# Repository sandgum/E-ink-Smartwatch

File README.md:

# Triangulate ES_01 E-ink Watch
---
An ultra-thin ESP32S3-based smartwatch (at just 5mm thick at its thickest point) which uses an E-ink display and two OLEDs to display information while consuming a small amount of power. The main E-ink panel is touch-enabled, with the two additional OLED panels above and below it displaying auxiliary information, such as notifications, background activities etc. 
The watch has built-in heart rate and spO2 sensing via an Analog Devices MAX30102, high-precision smart movement sensing via a Bosch BH260AP IMU and a Bosch BMP585 barometric pressure sensor.

*ACKNOWLEDGMENT: Most of the materials and the human hand model you see in the renders are not my own work, but is Royalty-free or CC0 licensed work legitimately downloaded from BlenderKit using their free plan*

---

To top it all off, the ES_01 is completely workout-friendly, with rubberised sides and no pesky side buttons that get pressed mid-pushup (Every physical input is at the top of the watch)!
The watch features a sleek design, with each component being laid out single file and in its own separate segment of the watch. These segments can all bend around the watch, preserving a uniform thickness all around, which also adds the benefit of being aesthetically pleasing.
The main microcontroller running the watch is an Espressif ESP32-S3 running with Bluetooth LE capabilities, which also allow for it to sync with a smartphone to relay notifications, workout, and weather data etc. through firmware based on ESP-IDF and host smartphone software for iPhone based on Swift (Coming soon, and Android support will come later!)

---
## PCB:

-  4 layers
-  Flex PCB
-  Single-sided component placement
-  0.2mm board thickness
-  Added 0.1mm FR4 stiffeners
-  All resistors and capacitors are 0402 size

*Schematics:*

*PCB Layout and render:*

---

## Enclosure:

- Main cases and top plates of easch segment 3D printed using an SLA/MSLA printer
- Main cases printed in Black resin from JLC3DP (can substitute with any rigid resin)
- Top plates printed in LEDO 6060 resin from JLC3DP (can substitute with any rigid resin)
- Bottom plates for OLED segments are CNC machined from 6061 Aluminium by JLCCNC (can substitute with any rigid material or also with SLA/MSLA printed resin)
- Bottom plate for main E-ink segment 3D printed using an SLM printer in 316L stainless steel (can substitute with other rigid metal with high thermal conductivity)

---

## Assembly instructions:

1. Use the solder stencil to squeegee solder paste onto main PCB
2. Place each component onto its respective pads on the main PCB
3. Use a hotplate or a reflow oven to reflow the solder paste underneath the components
4. Hand-solder a thin insulated wire (enamel insulated or rubber insulated) connecting the pads "BATT1_WIRE" together on the PCB
5. Create a solder bridge connecting the pads "GND_TO_GNDIO" and "GNDIO_TO_GND"
6. Create a solder bridge connecting the pads "GND_TO_GNDPWR" and "GNDPWR_TO_GND"
7. Assemble the two "end battery" segments by threading battery wires through them, placing the battery in and attaching the top plates to their respective main cases with superglue
8. Assemble the other battery segment and the haptic module segment in the same way, but thread the "end battery" wires through the dedicated channels in these segments, you should have two sets of two segments with four wires coming out of each set of segments
9. Take the main cases of the OLED modules and superglue the OLED displays into the top of each, making sure the flex cables poke through their dedicated holes
10. Do the same with the E-ink segment and the E-ink display
11. Attach each remaining top plate to its respective main case using superglue
12. Place and superglue the main Flex PCB into the bottom of the E-ink segment and the two OLED segments. The back of the PCB should face the displays
13. Thread the wires from the two sets of segments from step 8 through the holes in the side of the OLED modules and hand-solder the wires onto their respective pads
14. Plug in the flex cables from each display into thir respective FPC connectors on the main PCB
15. Superglue the bottom panels for the OLED segments onto their respective main cases
16. Apply thermal paste on the ESP32-S3 chip on the main PCB
17. Superglue threaded inserts in the two dedicated holes in the corners of the bottom panel for the E-ink segment
19. Superglue the bottom panel to the main case of the E-ink segment
20. Screw two screws into the holes in the top case of the E-ink segment until they mesh with the threaded inserts from the previous step
21. Take two more screws and cut off their entire threaded sections until just the heads remain. Superglue those heads in the holes in the other two corners of the top panel of the E-ink segment
22. Superglue the side TPU pieces to the sides of all the segments
23. Plug in a patch antenna into the exposed U.FL port on the back of the watch, guide the cable through its designated groove, and stick the patch antenna somewhere on the watch

---
## Bill of materials:

*Electronic Components: (Order quantities account for minimum order quantity of parts from the chosen retailer)*

| Manufacturer Part Number | Mfr.                        | Order Qty. | Unit Price(USD) | Ext.Price(USD) | Package                               | Description                                                                                                                | Product Link                                       |
|--------------------------|-----------------------------|------------|-----------------|----------------|---------------------------------------|----------------------------------------------------------------------------------------------------------------------------|----------------------------------------------------|
| CC0402JRNPO9BN110        | YAGEO                       | 100        | 0.0012          | 0.12           | 0402                                   | 11pF ±5% 50V Ceramic Capacitor NP0 0402                                                                                    | https://www.lcsc.com/product-detail/C527000.html   |
| GRM155R61E475ME15D       | muRata                      | 20         | 0.0377          | 0.75           | 0402                                   | 4.7uF ±20% 25V Ceramic Capacitor X5R 0402                                                                                  | https://www.lcsc.com/product-detail/C2858031.html  |
| ESP32-S3                 | ESPRESSIF                   | 1          | 2.7791          | 2.78           | QFN-56-EP(7x7)                         | 150Mbps 2.4GHz 2.412GHz~2.484GHz QFN-56-EP(7x7) RF Transceiver ICs RoHS                                                    | https://www.lcsc.com/product-detail/C2913192.html  |
| 2328702-6                | TE Connectivity             | 5          | 0.1654          | 0.83           | SMD,P=0.5mm,Surface Mount,Right Angle  | FFC/FPC Connector 6 Position 0.5mm Pitch Double-Sided Contacts, Top and Bottom Entry Surface Mount, Right Angle -40℃~+85℃  | https://www.lcsc.com/product-detail/C3151647.html  |
| FFC2B28-24-G             | Global Connector Technology | 1          | 0.5754          | 0.58           | SMD,P=0.5mm,Surface Mount,Right Angle  | FFC/FPC Connector 24 Position 0.5mm Pitch Double-Sided Contacts, Top and Bottom Entry Surface Mount, Right Angle -25℃~+85℃ | https://www.lcsc.com/product-detail/C3151659.html  |
| BHI260AP                 | Bosch                       | 1          | 8.7882          | 8.79           | LGA-44                                 | LGA-44 IMUs (Inertial Measurement Units) RoHS                                                                              | https://www.lcsc.com/product-detail/C3288651.html  |
| SI1308EDL-T1-GE3         | VISHAY                      | 5          | 0.1324          | 0.66           | SOT-323                                | N-Channel 30V 1.5A 0.4W Surface Mount SOT-323                                                                              | https://www.lcsc.com/product-detail/C469327.html   |
| XC6206P302MR             | HXY MOSFET                  | 50         | 0.0154          | 0.77           | SOT-23                                 | Linear Voltage Regulator IC Positive Fixed 1 Output 300mA SOT-23                                                           | https://www.lcsc.com/product-detail/C5148691.html  |
| MBR0530                  | Huixin                      | 20         | 0.0205          | 0.41           | SOD-123                                | 5.5A 30V 500mV@500mA 500mA SOD-123 Single Diodes RoHS                                                                     | https://www.lcsc.com/product-detail/C49435625.html |
| 0402WGF1004TCE           | UNI-ROYAL                   | 100        | 0.0006          | 0.06           | 0402                                   | 1MΩ ±1% 62.5mW 0402 Thick Film Resistor                                                                                    | https://www.lcsc.com/product-detail/C26083.html    |
| CL05A105KA5NQNC          | Samsung Electro-Mechanics   | 100        | 0.0030          | 0.30           | 0402                                   | 1uF ±10% 25V Ceramic Capacitor X5R 0402                                                                                    | https://www.lcsc.com/product-detail/C52923.html    |
| XL2EL89CPI-111YLC-40M    | YXC Crystal Oscillators     | 10         | 0.0578          | 0.58           | SMD3225-4P                             | Crystal 40MHz ±10ppm 15pF SMD3225-4P                                                                                       | https://www.lcsc.com/product-detail/C5444549.html  |
| TS-1088-AR02016          | XUNPU                       | 10         | 0.0421          | 0.42           | SMD,4x3mm                              | Tactile Switch SPST 160gf 2mm SMD (SMT) Tab 4mm x 3mm Surface Mount                                                        | https://www.lcsc.com/product-detail/C720477.html   |
| BSS138                   | R+O                         | 50         | 0.0170          | 0.85           | SOT-23                                 | N-Channel 50V 340mA 350mW Surface Mount SOT-23                                                                             | https://www.lcsc.com/product-detail/C7420339.html  |
| TCR2EF33,LM(CT           | TOSHIBA                     | 5          | 0.0829          | 0.41           | TSOT-25                                | Positive Fixed 3.3V TSOT-25 Voltage Regulators - Linear, Low Drop Out (LDO) Regulators RoHS                                | https://www.lcsc.com/product-detail/C843273.html   |
| LQG15HS3N3S02D           | muRata                      | 100        | 0.0076          | 0.76           | 0402                                   | 800mA 3.3nH 125mΩ 0402 Fixed Inductors RoHS                                                                                | https://www.lcsc.com/product-detail/C86064.html    |
| MRA4003T3G               | onsemi                      | 10         | 0.0873          | 0.87           | SMA(DO-214AC)                          | Diode 300V 1A Surface Mount SMA(DO-214AC)                                                                                  | https://www.lcsc.com/product-detail/C94410.html    |
| DRV2605LDGSR             | TI                          | 1          | 1.2502          | 1.3            | VSSOP-10-0.5mm                         | 2V~5.2V I2C VSSOP-10-0.5mm Motor Drivers, Controllers RoHS                                                                 | https://www.lcsc.com/product-detail/C527464.html   |
| LQG15HS2N0S02D           | muRata                      | 100        | 0.0081          | 0.81           | 0402                                   | 900mA 2nH 90mΩ 0402 Fixed Inductors RoHS                                                                                   | https://www.lcsc.com/product-detail/C18216.html    |
| 0402WGF5603TCE           | UNI-ROYAL                   | 100        | 0.0005          | 0.05           | 0402                                   | 560kΩ ±1% 62.5mW 0402 Thick Film Resistor                                                                                  | https://www.lcsc.com/product-detail/C132339.html   |
| CL05B103KB5NNNC          | Samsung Electro-Mechanics   | 100        | 0.0014          | 0.14           | 0402                                   | 10nF ±10% 50V Ceramic Capacitor X7R 0402                                                                                   | https://www.lcsc.com/product-detail/C15195.html    |
| 0402B102K500NT           | FH                          | 100        | 0.0011          | 0.11           | 0402                                   | 1nF ±10% 50V Ceramic Capacitor X7R 0402                                                                                    | https://www.lcsc.com/product-detail/C1523.html     |
| CL05B104KO5NNNC          | Samsung Electro-Mechanics   | 100        | 0.0012          | 0.12           | 0402                                   | 100nF ±10% 16V Ceramic Capacitor X7R 0402                                                                                  | https://www.lcsc.com/product-detail/C1525.html     |
| 0402CG1R0C500NT          | FH                          | 100        | 0.0012          | 0.12           | 0402                                   | 1pF 50V Ceramic Capacitor C0G 0402                                                                                         | https://www.lcsc.com/product-detail/C1550.html     |
| CL05A106MQ5NUNC          | Samsung Electro-Mechanics   | 100        | 0.0044          | 0.44           | 0402                                   | 10uF ±20% 6.3V Ceramic Capacitor X5R 0402                                                                                  | https://www.lcsc.com/product-detail/C15525.html    |
| CL05B224KO5NNNC          | Samsung Electro-Mechanics   | 100        | 0.0044          | 0.44           | 0402                                   | 220nF ±10% 16V Ceramic Capacitor X7R 0402                                                                                  | https://www.lcsc.com/product-detail/C16772.html    |
| BMP585                   | Bosch                       | 1          | 2.2083          | 2.21           | LGA-9(3.3x3.3)                         | 30Kpa~1.25bar LGA-9(3.3x3.3) Pressure Sensors, Transducers RoHS                                                            | https://www.lcsc.com/product-detail/C18184976.html |
| 0402WGF1001TCE           | UNI-ROYAL                   | 100        | 0.0006          | 0.06           | 0402                                   | 1kΩ ±1% 62.5mW 0402 Thick Film Resistor                                                                                    | https://www.lcsc.com/product-detail/C11702.html    |
| LD39200PU33R             | ST                          | 1          | 1.2693          | 1.27           | DFN-6(3x3)                             | Positive Fixed 3.3V DFN-6(3x3) Voltage Regulators - Linear, Low Drop Out (LDO) Regulators RoHS                             | https://www.lcsc.com/product-detail/C222192.html   |
| CL05A475MP5NRNC          | Samsung Electro-Mechanics   | 50         | 0.0048          | 0.24           | 0402                                   | 4.7uF ±20% 10V Ceramic Capacitor X5R 0402                                                                                  | https://www.lcsc.com/product-detail/C23733.html    |
| 0402WGF220JTCE           | UNI-ROYAL                   | 100        | 0.0007          | 0.07           | 0402                                   | 22Ω ±1% 62.5mW 0402 Thick Film Resistor                                                                                    | https://www.lcsc.com/product-detail/C25092.html    |
| 0402WGF220KTCE           | UNI-ROYAL                   | 100        | 0.0009          | 0.09           | 0402                                   | 2.2Ω ±1% 62.5mW 0402 Thick Film Resistor                                                                                   | https://www.lcsc.com/product-detail/C25101.html    |
| 0402WGF1002TCE           | UNI-ROYAL                   | 100        | 0.0006          | 0.06           | 0402                                   | 10kΩ ±1% 62.5mW 0402 Thick Film Resistor                                                                                   | https://www.lcsc.com/product-detail/C25744.html    |
| 0402WGF2201TCE           | UNI-ROYAL                   | 100        | 0.0006          | 0.06           | 0402                                   | 2.2kΩ ±1% 62.5mW 0402 Thick Film Resistor                                                                                  | https://www.lcsc.com/product-detail/C25879.html    |
| 0402WGF4701TCE           | UNI-ROYAL                   | 100        | 0.0006          | 0.06           | 0402                                   | 4.7kΩ ±1% 62.5mW 0402 Thick Film Resistor                                                                                  | https://www.lcsc.com/product-detail/C25900.html    |
| ANR4012T470M             | APV                         | 10         | 0.0517          | 0.52           | SMD,4x4mm                              | 47uH Magnetic Shielded Inductor 500mA SMD,4x4mm Fixed Inductors RoHS                                                       | https://www.lcsc.com/product-detail/C7497063.html  |
| MAX30102EFD+T            | MAXIM                       | 1          | 13.7281         | 13.73          | OESIP-14                               | I2C OESIP-14 Specialized Sensors RoHS                                                                                      | https://www.lcsc.com/product-detail/C6454833.html  |
| LW06121                  | WENDA                       | 100        | 0.07            | 7              | SMD,P=0.62mm,Surface Mount,Right Angle | 1.2H 14Pin 0.62mm Pitch OLED FPC/FFC Upper Contact Pull-Out Horizontal SMD Flat Connector                                 | https://www.alibaba.com/product-detail/WENDA-LW06121-1-2H-14Pin-0_1601292173873.html |
| 1N4148                   | onsemi                      | 50         | 0.0221          | 1.11           | DO-35                                  | Diode 100V 200mA Through Hole DO-35                                                                                        | https://www.lcsc.com/product-detail/C258182.html   |
| GDEY0154D67-T03          | Goodisplay                  | 1          | 11.32           | 11.32          | -                                      | 1.54Inch Touch E-Paper 200x200 E-Ink Display                                                                               | https://www.aliexpress.com/item/1005005200574055.html |
| SSD1306                  | -                           | 2          | 0.72            | 1.44           | -                                      | 0.91 Inch I2C OLED Module                                                                                                  | https://www.aliexpress.com/item/1005004415958608.html?spm=a2g0o.tesla.0.0.4820nU7CnU7Cr1&pdp_npi=6%40dis%21AUD%21AU%241.39%21AU%241.05%21%21%21%21%21%402103122117624689217517794e3108%2112000046550658291%21btfpre%21%21%21%211%210%21&afTraceInfo=1005004415958608__pc__c_ppc_item_bridge_pc_main__vt8pak6__1762468921809 |
| 401225                   | -                           | 3          | 2.66            | 7.98           | -                                      | 3.7V 100mAh Lithium Polymer Lipo Rechargeable Battery                                                                      | https://www.aliexpress.com/item/1005006129236699.html?spm=a2g0o.cart.0.0.157538daxZfUfb&mp=1&pdp_npi=5%40dis%21AUD%21AUD%204.73%21AUD%204.02%21%21AUD%204.02%21%21%21%402103212317648973370843232e461d%2112000035892453159%21ct%21AU%216047249797%21%211%210 |
| 0619AAC                  | -                           | 1          | 3.06            | 3.06           | -                                      | Brushless X-axis 1.2V 100mA Max Precision Vibration Motor                                                                  | https://www.aliexpress.com/item/1005006421331249.html?spm=a2g0o.tesla.0.0.24f1nmtsnmts4h&pdp_npi=6%40dis%21AUD%21AU%244.13%21AU%241.54%21%21%21%21%21%402101d9ef17624709252885249e887e%2112000049883253246%21btfpre%21%21%21%211%210%21&afTraceInfo=1005006421331249__pc__c_ppc_item_bridge_pc_main__epipcn9__1762470925359 |
| TS-A002                  | -                           | 20         | 0.069           | 1.38           | -                                      | Momentary Tact Switch SMD                                                                                                  | https://www.aliexpress.com/item/1005008702742151.html?spm=a2g0o.cart.0.0.785138daOe1hVa&mp=1&pdp_npi=5%40dis%21USD%21USD%201.38%21USD%201.38%21%21USD%201.38%21%21%21%4021033d1217668082665115137ee51b%2112000046642944142%21ct%21AU%216047249797%21%211%210 |
| -                        | -                           | 50         | 0.0264          | 1.32           | -                                      | M1.4 Torx countersunk machine screw 4mm length                                                                             | https://www.aliexpress.com/item/33006942612.html?spm=a2g0o.cart.0.0.172438dayDrOXJ&mp=1&pdp_npi=5%40dis%21USD%21USD%201.32%21USD%201.32%21%21USD%201.32%21%21%21%402103212317668074428231957e8041%2167012387977%21ct%21AU%216047249797%21%211%210 |
| -                        | -                           | 50        | 0.0244          | 1.22            | -                                      | M1.4 Brass threaded inserts 1.5mm length                                                                                   | https://www.aliexpress.com/item/1005007653131713.html?spm=a2g0o.cart.0.0.785138daOe1hVa&mp=1&pdp_npi=5%40dis%21USD%21USD%201.36%21USD%201.22%21%21USD%201.22%21%21%21%402101e2b217668079638444750e2ddc%2112000041667111405%21ct%21AU%216047249797%21%211%210&pdp_ext_f=%7B%22cart2PdpParams%22%3A%7B%22pdpBusinessMode%22%3A%22retail%22%7D%7D |

Total: $85.43 USD

*Manufactured Components*

| Description | Manufacturer | Material | Price (USD) |
|-------------|--------------|----------|-------------|
| 3D Printed Enclosure Main Cases | JLC3DP | Black Resin | 7.05 |
| 3D Printed Enclosure Top Plates | JLC3DP | LEDO 6060 Resin | 2.11 |
| CNC Machined OLED Segment Bottom Plates | JLCCNC | Aluminium 6061 | 17.46 |
| SLM 3D Printed Main Segment Bottom Plate | JLC3DP | 316L Stainless Steel | 8.39 |
| Main 4-layer Flex PCB | JLCPCB | Yellow 0.2mm Polyimide with 0.1mm FR4 Stiffener | 94.00 |
| SMD Stencil for Main Flex PCB | JLCPCB | Steel | 7.47 |

Total: $136.48 USD

---
## Grand Total (Excl. Shipping): $221.91 USD
---

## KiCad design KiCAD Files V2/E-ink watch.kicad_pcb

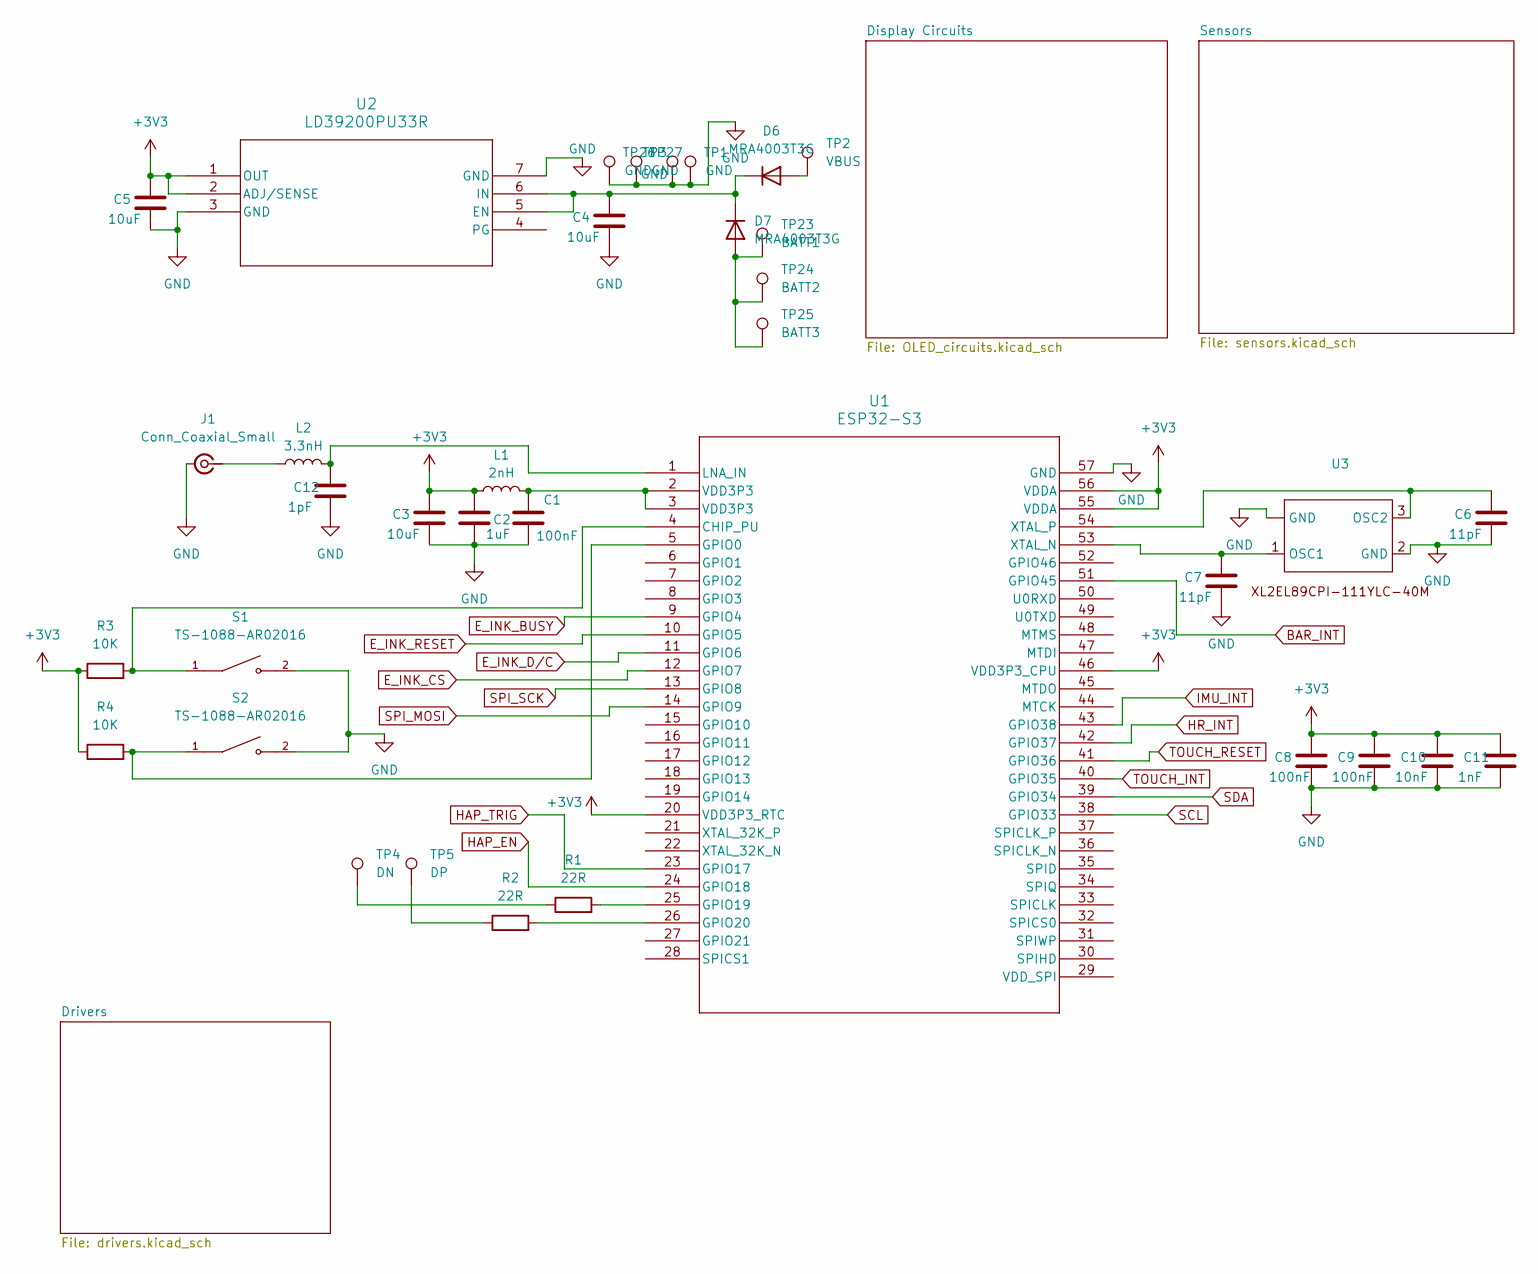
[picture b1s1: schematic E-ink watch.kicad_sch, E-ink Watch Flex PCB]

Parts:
C1, C8, C9: 100nF; C_0402_1005Metric_Pad0.74x0.62mm_HandSolder
C2: 1uF; C_0402_1005Metric_Pad0.74x0.62mm_HandSolder
C3, C4, C5: 10uF; C_0402_1005Metric_Pad0.74x0.62mm_HandSolder
C6, C7: 11pF; C_0402_1005Metric_Pad0.74x0.62mm_HandSolder
C10: 10nF; C_0402_1005Metric_Pad0.74x0.62mm_HandSolder
C11: 1nF; C_0402_1005Metric_Pad0.74x0.62mm_HandSolder
C12: 1pF; C_0402_1005Metric_Pad0.74x0.62mm_HandSolder
D6, D7: MRA4003T3G; D_SMA
J1: Conn_Coaxial_Small; U.FL_Hirose_U.FL-R-SMT-1_Vertical
L1: 2nH; L_0402_1005Metric_Pad0.77x0.64mm_HandSolder
L2: 3.3nH; L_0402_1005Metric_Pad0.77x0.64mm_HandSolder
R1, R2: 22R; R_0402_1005Metric_Pad0.72x0.64mm_HandSolder
R3, R4: 10K; R_0402_1005Metric_Pad0.72x0.64mm_HandSolder
S1, S2: TS-1088-AR02016; SW_TS-1088-AR02016; PARTREV N/A
TP1, TP3, TP26, TP27: GND; TestPoint_Pad_1.5x1.5mm
TP2: VBUS; TestPoint_Pad_1.5x1.5mm
TP4: DN; TestPoint_Pad_1.5x1.5mm
TP5: DP; TestPoint_Pad_1.5x1.5mm
TP23: BATT1; TestPoint_Pad_1.5x1.5mm
TP24: BATT2; TestPoint_Pad_1.5x1.5mm
TP25: BATT3; TestPoint_Pad_1.5x1.5mm
U1: ESP32-S3; QFN56_7X7_EXP
U2: LD39200PU33R; SON_DFN6_3X3_STM
U3: Untitled

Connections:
+3V3: C2.1, C3.1, C5.1, C8.1, C9.1, C10.1, C11.1, L1.1, R3.1, R4.1, U1.20 (VDD3P3_RTC), U1.46 (VDD3P3_CPU), U1.55 (VDDA), U1.56 (VDDA), U2.1 (OUT), U2.2 (ADJ/SENSE); also elsewhere on the board
BAR_INT: U1.51 (GPIO45); also elsewhere on the board
E_INK_BUSY: U1.9 (GPIO4); also elsewhere on the board
E_INK_CS: U1.12 (GPIO7); also elsewhere on the board
E_INK_D/C: U1.11 (GPIO6); also elsewhere on the board
E_INK_RESET: U1.10 (GPIO5); also elsewhere on the board
GND: C1.2, C2.2, C3.2, C4.2, C5.2, C6.2, C7.2, C8.2, C9.2, C10.2, C11.2, C12.2, J1.2 (Ext), S1.2, S2.2, TP1.1, TP3.1, TP26.1, TP27.1, U1.57 (GND), U2.3 (GND), U2.7 (GND), U3. (GND), U3.2 (GND), U3.4; also elsewhere on the board
HAP_EN: U1.24 (GPIO18); also elsewhere on the board
HAP_TRIG: U1.23 (GPIO17); also elsewhere on the board
HR_INT: U1.42 (GPIO37); also elsewhere on the board
IMU_INT: U1.43 (GPIO38); also elsewhere on the board
unnamed: C1.1, L1.2, U1.2 (VDD3P3), U1.3 (VDD3P3)
unnamed: D6.2 (A), TP2.1
unnamed: C4.1, D6.1 (K), D7.1 (K), U2.5 (EN), U2.6 (IN)
unnamed: D7.2 (A), TP23.1, TP24.1, TP25.1
unnamed: J1.1 (In), L2.1
unnamed: R1.1, TP4.1
unnamed: R2.1, TP5.1
unnamed: R3.2, S1.1, U1.4 (CHIP_PU)
unnamed: R4.2, S2.1, U1.5 (GPIO0)
unnamed: R1.2, U1.25 (GPIO19)
unnamed: R2.2, U1.26 (GPIO20)
unnamed: C12.1, L2.2, U1.1 (LNA_IN)
unnamed: C7.1, U1.53 (XTAL_N), U3.1 (OSC1)
unnamed: C6.1, U1.54 (XTAL_P), U3.3 (OSC2)
SCL: U1.38 (GPIO33); also elsewhere on the board
SDA: U1.39 (GPIO34); also elsewhere on the board
SPI_MOSI: U1.14 (GPIO9); also elsewhere on the board
SPI_SCK: U1.13 (GPIO8); also elsewhere on the board
TOUCH_INT: U1.40 (GPIO35); also elsewhere on the board
TOUCH_RESET: U1.41 (GPIO36); also elsewhere on the board

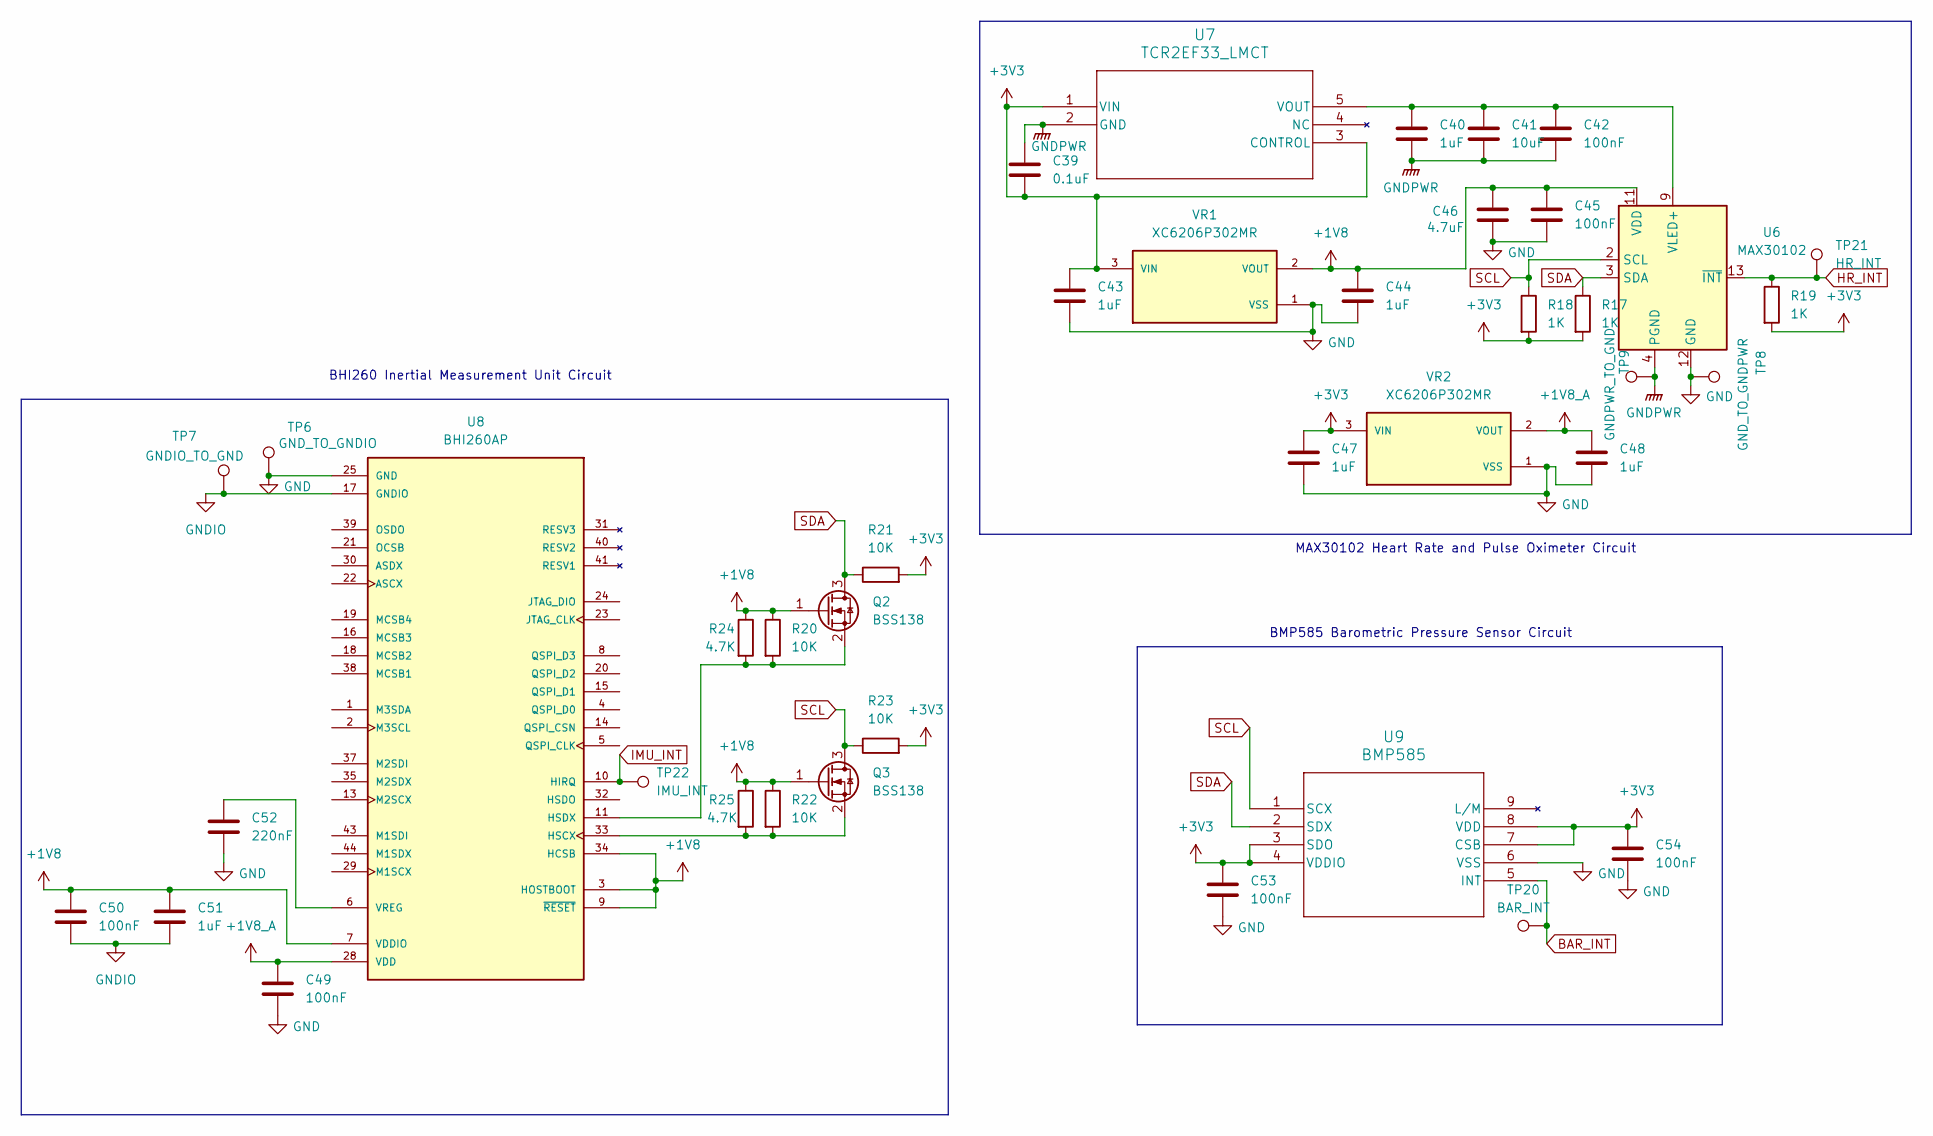
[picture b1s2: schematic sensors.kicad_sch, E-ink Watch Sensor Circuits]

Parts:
C39: 0.1uF; C_0402_1005Metric_Pad0.74x0.62mm_HandSolder
C40, C43, C44, C47, C48, C51: 1uF; C_0402_1005Metric_Pad0.74x0.62mm_HandSolder
C41: 10uF; C_0402_1005Metric_Pad0.74x0.62mm_HandSolder
C42, C45, C49, C50, C53, C54: 100nF; C_0402_1005Metric_Pad0.74x0.62mm_HandSolder
C46: 4.7uF; C_0402_1005Metric_Pad0.74x0.62mm_HandSolder
C52: 220nF; C_0402_1005Metric_Pad0.74x0.62mm_HandSolder
Q2, Q3: BSS138; SOT-23
R17, R18, R19: 1K; R_0402_1005Metric_Pad0.72x0.64mm_HandSolder
R20, R21, R22, R23: 10K; R_0402_1005Metric_Pad0.72x0.64mm_HandSolder
R24, R25: 4.7K; R_0402_1005Metric_Pad0.72x0.64mm_HandSolder
TP6: GND_TO_GNDIO; TestPoint_Pad_1.5x1.5mm
TP7: GNDIO_TO_GND; TestPoint_Pad_1.5x1.5mm
TP8: GND_TO_GNDPWR; TestPoint_Pad_1.5x1.5mm
TP9: GNDPWR_TO_GND; TestPoint_Pad_1.5x1.5mm
TP20: BAR_INT; TestPoint_Pad_D1.0mm
TP21: HR_INT; TestPoint_Pad_D1.0mm
TP22: IMU_INT; TestPoint_Pad_D1.0mm
U6: MAX30102; Maxim_OLGA-14_3.3x5.6mm_P0.8mm
U7: TCR2EF33_LMCT; SOT-25 SMV_TOS
U8: BHI260AP; XDCR_BHI260AP; PARTREV 1.1
U9: BMP585; LGA9_BMP585_BOS
VR1, VR2: XC6206P302MR; SOT95P280X130-3N; PARTREV N/A

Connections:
+1V8: C44.1, C45.1, C46.1, C50.1, C51.1, Q2.1 (G), Q3.1 (G), R20.1, R22.1, R24.1, R25.1, U6.11 (VDD), U8.3 (HOSTBOOT), U8.7 (VDDIO), U8.9 (~RESET), U8.12 (VDDIO), U8.34 (HCSB), U8.42 (VDDIO), VR1.2 (VOUT)
+1V8_A: C48.1, C49.1, U8.28 (VDD), VR2.2 (VOUT)
+3V3: C39.2, C43.1, C47.1, C53.1, C54.1, R17.2, R18.2, R19.2, R21.2, R23.2, U7.1 (VIN), U7.3 (CONTROL), U9.3 (SDO), U9.4 (VDDIO), U9.7 (CSB), U9.8 (VDD), VR1.3 (VIN), VR2.3 (VIN); also elsewhere on the board
BAR_INT: TP20.1, U9.5 (INT); also elsewhere on the board
GND: C43.2, C44.2, C45.2, C46.2, C47.2, C48.2, C49.2, C52.2, C53.2, C54.2, TP6.1, TP8.1, U6.12 (GND), U8.25 (GND), U8.26 (GND), U8.27 (GND), U9.6 (VSS), VR1.1 (VSS), VR2.1 (VSS); also elsewhere on the board
GNDIO: C50.2, C51.2, TP7.1, U8.17 (GNDIO), U8.36 (GNDIO)
GNDPWR: C39.1, C40.2, C41.2, C42.2, TP9.1, U6.4 (PGND), U7.2 (GND)
HR_INT: R19.1, TP21.1, U6.13 (~INT); also elsewhere on the board
IMU_INT: TP22.1, U8.10 (HIRQ); also elsewhere on the board
unnamed: Q2.2 (S), R20.2, R24.2, U8.11 (HSDX)
unnamed: Q3.2 (S), R22.2, R25.2, U8.33 (HSCX)
unnamed: C40.1, C41.1, C42.1, U6.9 (VLED+), U6.10 (VLED+), U7.5 (VOUT)
unnamed: C52.1, U8.6 (VREG)
SCL: Q3.3 (D), R18.1, R23.1, U6.2 (SCL), U9.1 (SCX); also elsewhere on the board
SDA: Q2.3 (D), R17.1, R21.1, U6.3 (SDA), U9.2 (SDX); also elsewhere on the board

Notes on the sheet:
MAX30102 Heart Rate and Pulse Oximeter Circuit
BHI260 Inertial Measurement Unit Circuit
BMP585 Barometric Pressure Sensor Circuit

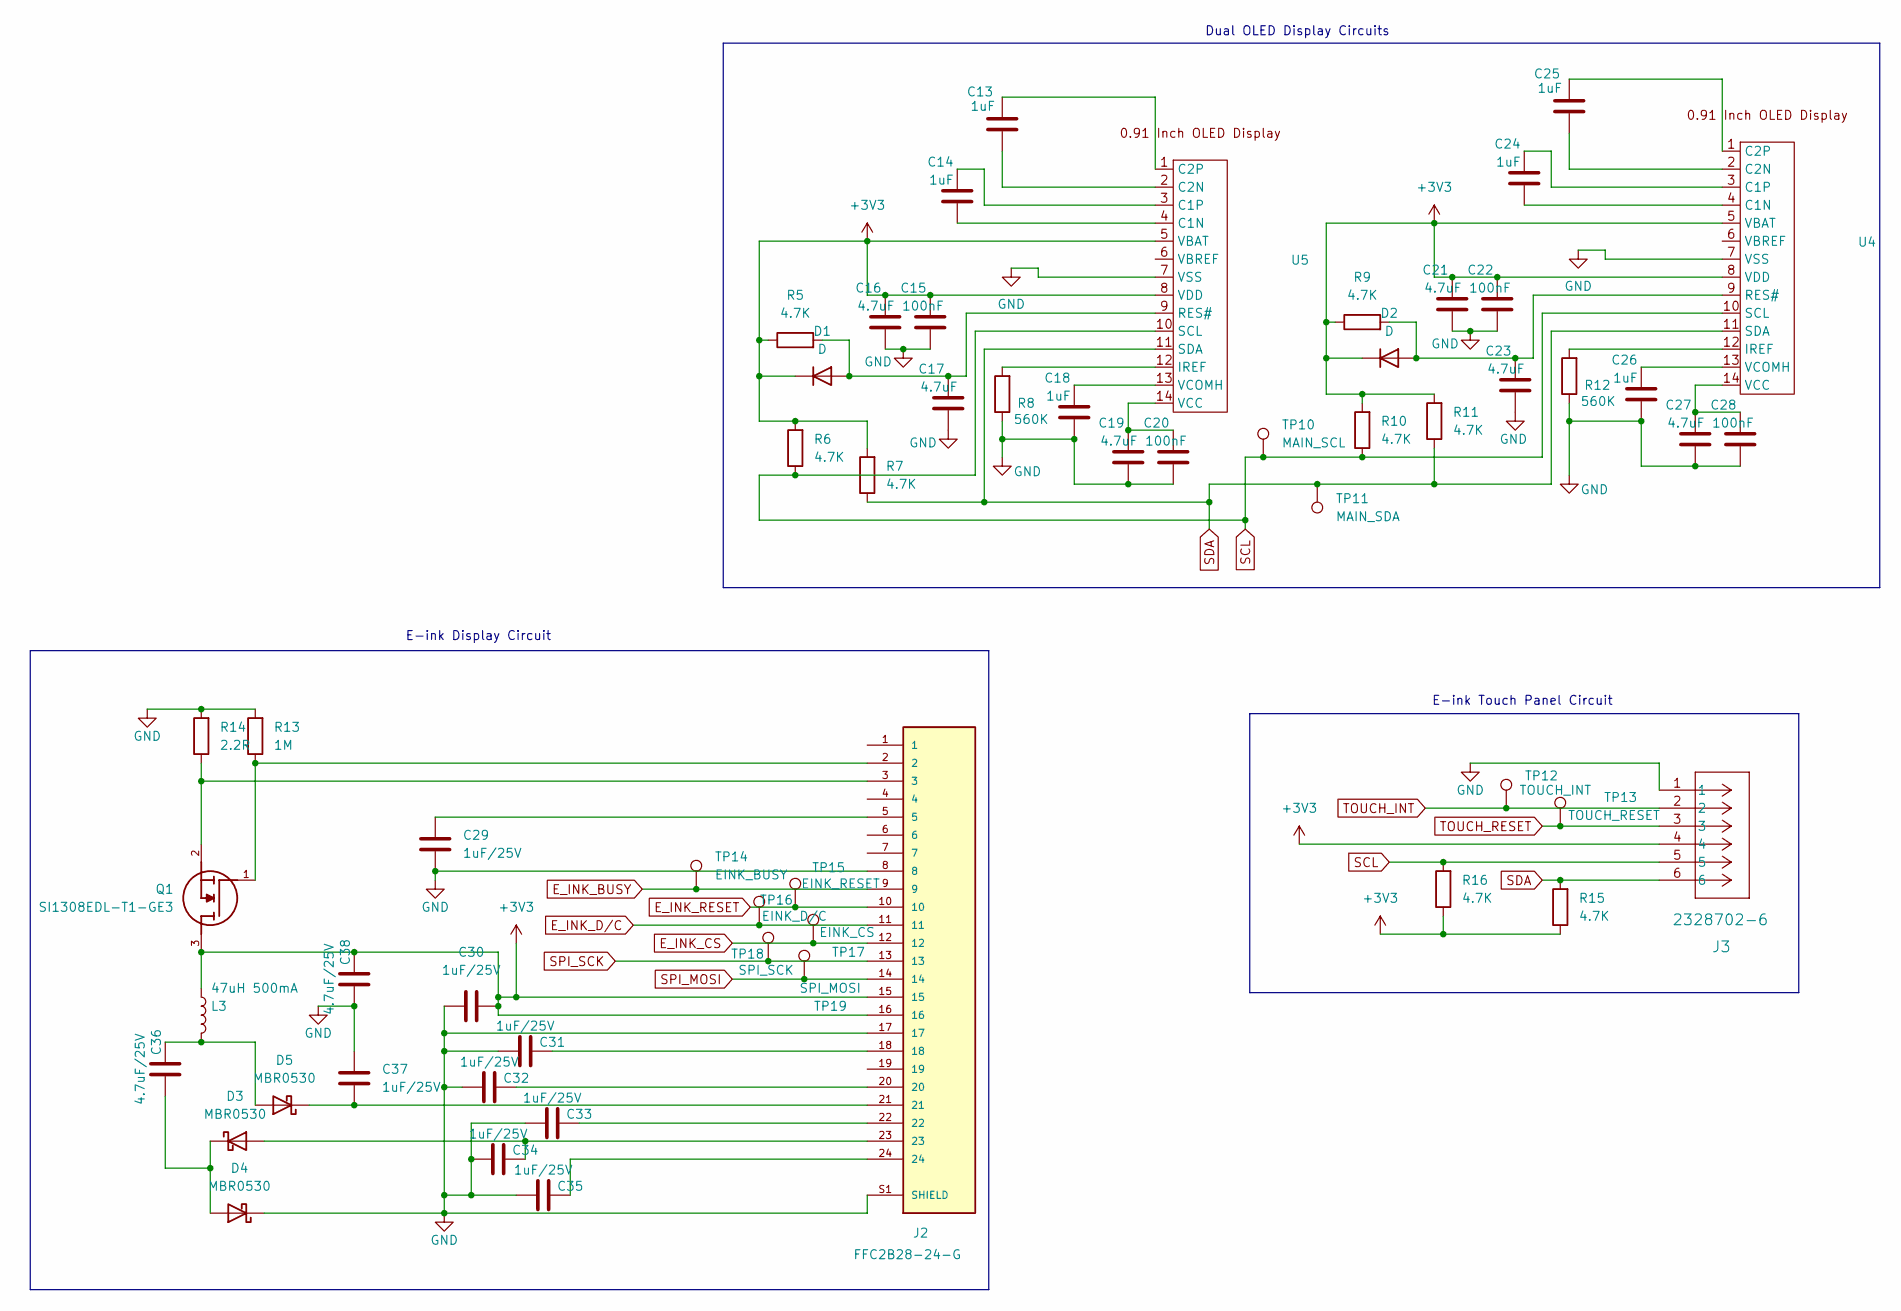
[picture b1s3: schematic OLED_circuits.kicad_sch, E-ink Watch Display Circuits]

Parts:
C13, C14, C18, C24, C25, C26: 1uF; C_0402_1005Metric_Pad0.74x0.62mm_HandSolder
C15, C20, C22, C28: 100nF; C_0402_1005Metric_Pad0.74x0.62mm_HandSolder
C16, C17, C19, C21, C23, C27: 4.7uF; C_0402_1005Metric_Pad0.74x0.62mm_HandSolder
C29, C30, C31, C32, C33, C34, C35, C37: 1uF/25V; C_0402_1005Metric_Pad0.74x0.62mm_HandSolder
C36, C38: 4.7uF/25V; C_0402_1005Metric_Pad0.74x0.62mm_HandSolder
D1, D2: D; D_DO-35_SOD27_P7.62mm_Horizontal
D3, D4, D5: MBR0530; D_0805_2012Metric_Pad1.15x1.40mm_HandSolder
J2: FFC2B28-24-G; GCT_FFC2B28-24-G; PARTREV A
J3: 2328702-6; CONN6_2328702-6_TEC
L3: 47uH 500mA; Untitled
Q1: SI1308EDL-T1-GE3; SOT65P210X110-3N; Mouser_Part_Number 78-SI1308EDL-T1-GE3
R5, R6, R7, R9, R10, R11, R15, R16: 4.7K; R_0402_1005Metric_Pad0.72x0.64mm_HandSolder
R8, R12: 560K; R_0402_1005Metric_Pad0.72x0.64mm_HandSolder
R13: 1M; R_0402_1005Metric_Pad0.72x0.64mm_HandSolder
R14: 2.2R; R_0402_1005Metric_Pad0.72x0.64mm_HandSolder
TP10: MAIN_SCL; TestPoint_Pad_D1.0mm
TP11: MAIN_SDA; TestPoint_Pad_D1.0mm
TP12: TOUCH_INT; TestPoint_Pad_D1.0mm
TP13: TOUCH_RESET; TestPoint_Pad_D1.0mm
TP14: EINK_BUSY; TestPoint_Pad_D1.0mm
TP15: EINK_RESET; TestPoint_Pad_D1.0mm
TP16: EINK_D/C; TestPoint_Pad_D1.0mm
TP17: EINK_CS; TestPoint_Pad_D1.0mm
TP18: SPI_SCK; TestPoint_Pad_D1.0mm
TP19: SPI_MOSI; TestPoint_Pad_D1.0mm
U4, U5: Untitled

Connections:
+3V3: C15.1, C16.1, C21.1, C22.1, C30.2, C38.2, D1.1 (K), D2.1 (K), J2.15, J2.16, J3.4, L3.1, Q1.3, R5.1, R6.2, R7.2, R9.1, R10.2, R11.2, R15.1, R16.1, U4.5 (VBAT), U4.8 (VDD), U5.5 (VBAT), U5.8 (VDD); also elsewhere on the board
E_INK_BUSY: J2.9, TP14.1; also elsewhere on the board
E_INK_CS: J2.12, TP17.1; also elsewhere on the board
E_INK_D/C: J2.11, TP16.1; also elsewhere on the board
E_INK_RESET: J2.10, TP15.1; also elsewhere on the board
GND: C15.2, C16.2, C17.2, C18.2, C19.2, C20.2, C21.2, C22.2, C23.2, C26.2, C27.2, C28.2, C29.2, C30.1, C31.1, C32.1, C33.1, C34.1, C35.1, C37.1, C38.1, D4.1 (K), J2.8, J2.17, J2.S1 (SHIELD), J2.S2 (SHIELD), J3.1, R8.1, R12.1, R13.2, R14.2, U4.7 (VSS), U5.7 (VSS); also elsewhere on the board
unnamed: C29.1, J2.5
unnamed: C31.2, J2.18
unnamed: C32.2, J2.20
unnamed: C33.2, J2.22
unnamed: C35.2, J2.24
unnamed: C17.1, D1.2 (A), R5.2, U5.9 (RES#)
unnamed: C23.1, D2.2 (A), R9.2, U4.9 (RES#)
unnamed: C34.2, D3.2 (A), J2.23
unnamed: C36.1, D3.1 (K), D4.2 (A)
unnamed: C36.2, D5.2 (A), L3.2
unnamed: C37.2, D5.1 (K), J2.21
unnamed: J2.2, Q1.1, R13.1
unnamed: J2.3, Q1.2, R14.1
unnamed: C24.2, U4.4 (C1N)
unnamed: C24.1, U4.3 (C1P)
unnamed: C25.2, U4.2 (C2N)
unnamed: C25.1, U4.1 (C2P)
unnamed: R12.2, U4.12 (IREF)
unnamed: C27.1, C28.1, U4.14 (VCC)
unnamed: C26.1, U4.13 (VCOMH)
unnamed: C14.2, U5.4 (C1N)
unnamed: C14.1, U5.3 (C1P)
unnamed: C13.2, U5.2 (C2N)
unnamed: C13.1, U5.1 (C2P)
unnamed: R8.2, U5.12 (IREF)
unnamed: C19.1, C20.1, U5.14 (VCC)
unnamed: C18.1, U5.13 (VCOMH)
SCL: J3.5, R6.1, R10.1, R16.2, TP10.1, U4.10 (SCL), U5.10 (SCL); also elsewhere on the board
SDA: J3.6, R7.1, R11.1, R15.2, TP11.1, U4.11 (SDA), U5.11 (SDA); also elsewhere on the board
SPI_MOSI: J2.14, TP19.1; also elsewhere on the board
SPI_SCK: J2.13, TP18.1; also elsewhere on the board
TOUCH_INT: J3.2, TP12.1; also elsewhere on the board
TOUCH_RESET: J3.3, TP13.1; also elsewhere on the board

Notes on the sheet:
E-ink Display Circuit
Dual OLED Display Circuits
E-ink Touch Panel Circuit

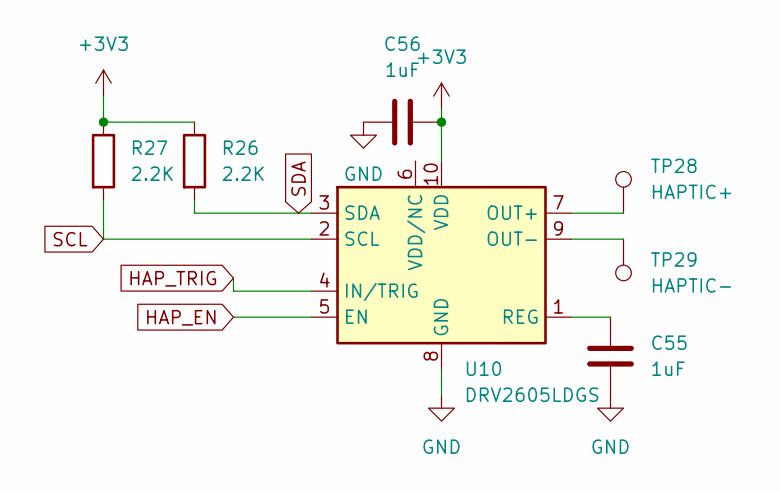
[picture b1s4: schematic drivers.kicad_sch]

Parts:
C55, C56: 1uF; C_0402_1005Metric_Pad0.74x0.62mm_HandSolder
R26, R27: 2.2K; R_0402_1005Metric_Pad0.72x0.64mm_HandSolder
TP28: HAPTIC+; TestPoint_Pad_1.5x1.5mm
TP29: HAPTIC-; TestPoint_Pad_1.5x1.5mm
U10: DRV2605LDGS; VSSOP-10_3x3mm_P0.5mm

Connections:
+3V3: C56.2, R26.1, R27.1, U10.10 (VDD); also elsewhere on the board
GND: C55.2, C56.1, U10.8 (GND); also elsewhere on the board
HAP_EN: U10.5 (EN); also elsewhere on the board
HAP_TRIG: U10.4 (IN/TRIG); also elsewhere on the board
unnamed: TP28.1, U10.7 (OUT+)
unnamed: TP29.1, U10.9 (OUT-)
unnamed: C55.1, U10.1 (REG)
SCL: R27.2, U10.2 (SCL); also elsewhere on the board
SDA: R26.2, U10.3 (SDA); also elsewhere on the board

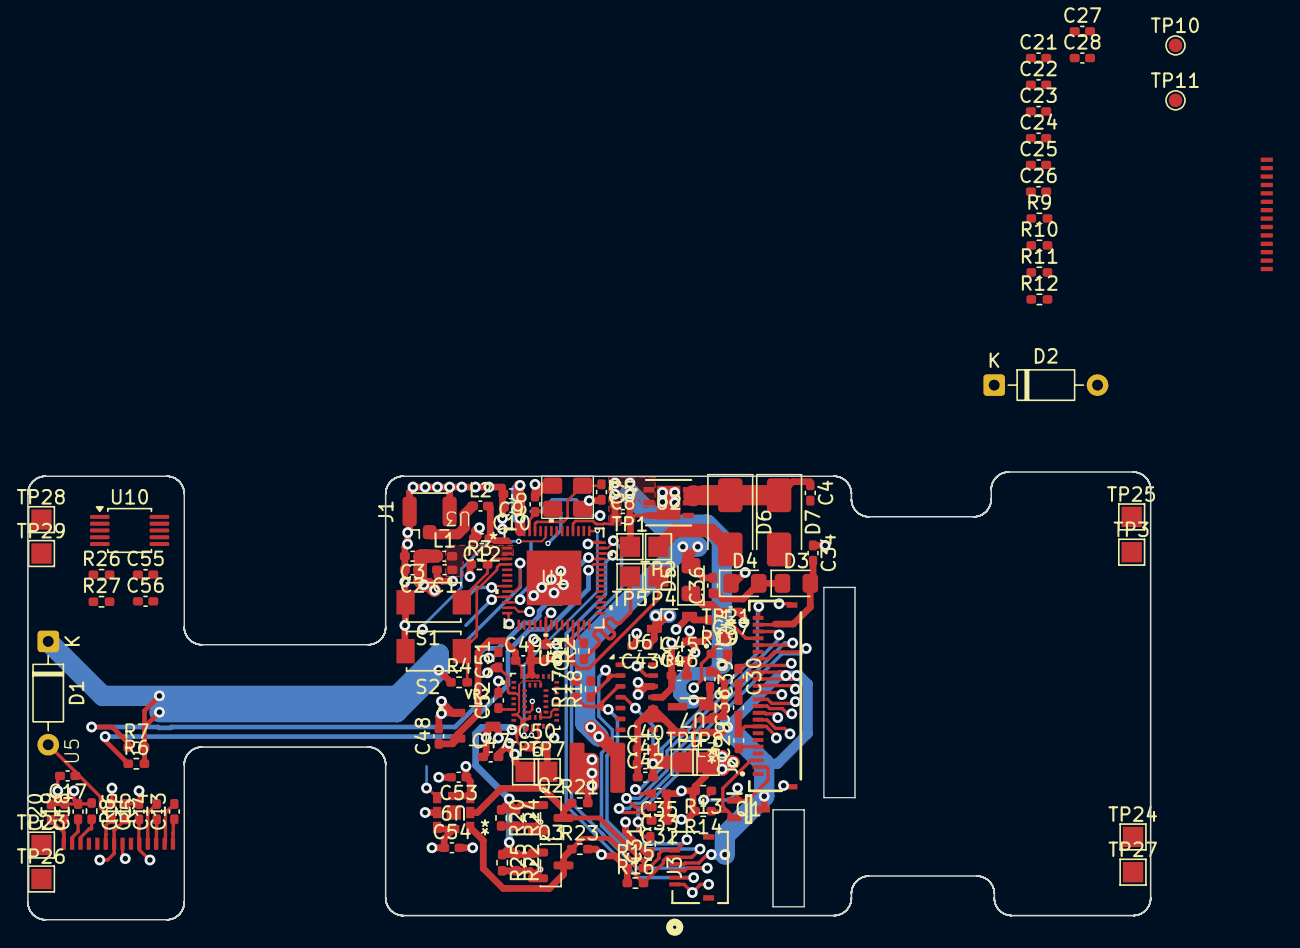
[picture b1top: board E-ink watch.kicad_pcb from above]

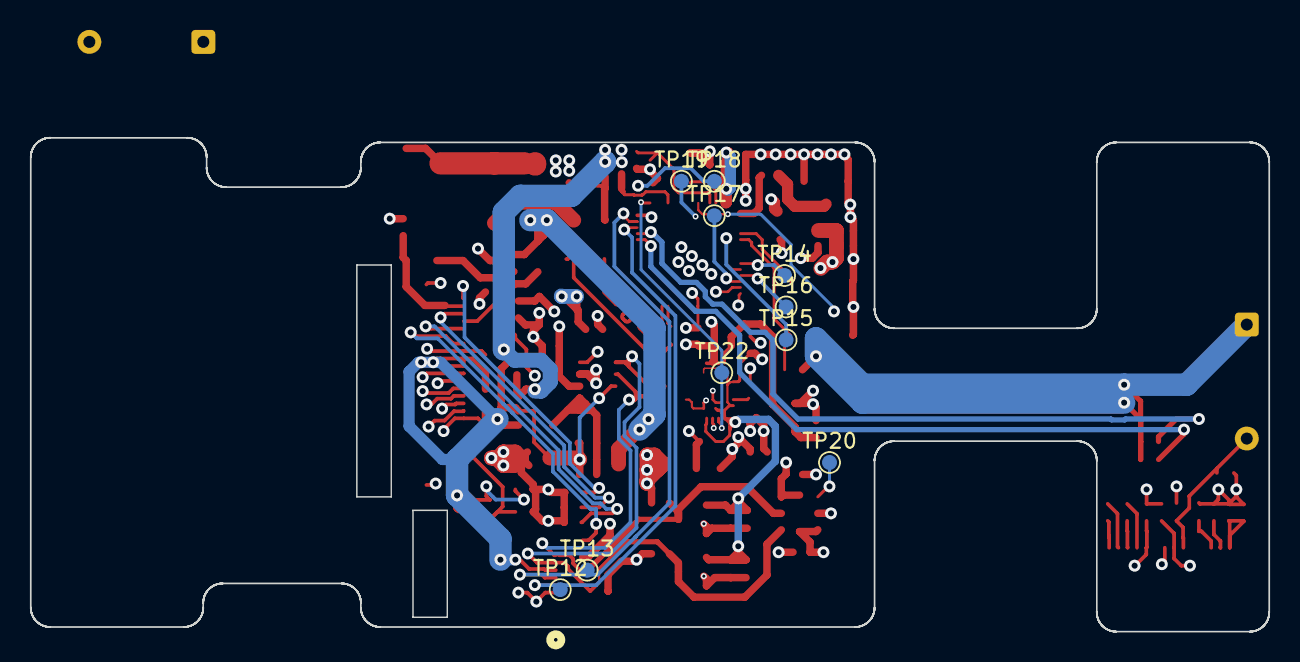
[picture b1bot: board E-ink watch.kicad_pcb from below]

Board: 4 copper layers, 82.8 x 33.0 mm, 142 parts (10 on the bottom side), 69 nets.

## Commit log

2025-12-11 Updated KiCAD files to include finished schematic
2025-12-16 Add updated enclosure STEP files
    Bottom plates and main cases of the end battery segments, the main battery segment and the haptic segment have been merged to make sure all parts comply with JLC3DP minimum printing restrictions
2025-12-16 Added PCB schematics in the form of PDFs
2025-12-23 Update README.md with new Blender renders
2025-12-23 Update README with PCB BoM and other PCB stuff
2025-12-25 Change Folders Layout
2025-12-25 Add final CAD folder (as per Blueprint guidelines)
2025-12-25 Update README.md with acknowledgment of Blender Render materials
2025-12-25 Update README.md with assembly instructions
2025-12-25 Add both BOM Files as CSV
2025-12-25 Create JOURNAL.md (empty for now)
2025-12-25 Fix table formatting error in README.md
2025-12-25 Remove link to Hack Club Blueprint Journal (JOURNAL.md is done)
2025-12-27 Update BOM in README.md with screws and inserts, and update assembly instructions
